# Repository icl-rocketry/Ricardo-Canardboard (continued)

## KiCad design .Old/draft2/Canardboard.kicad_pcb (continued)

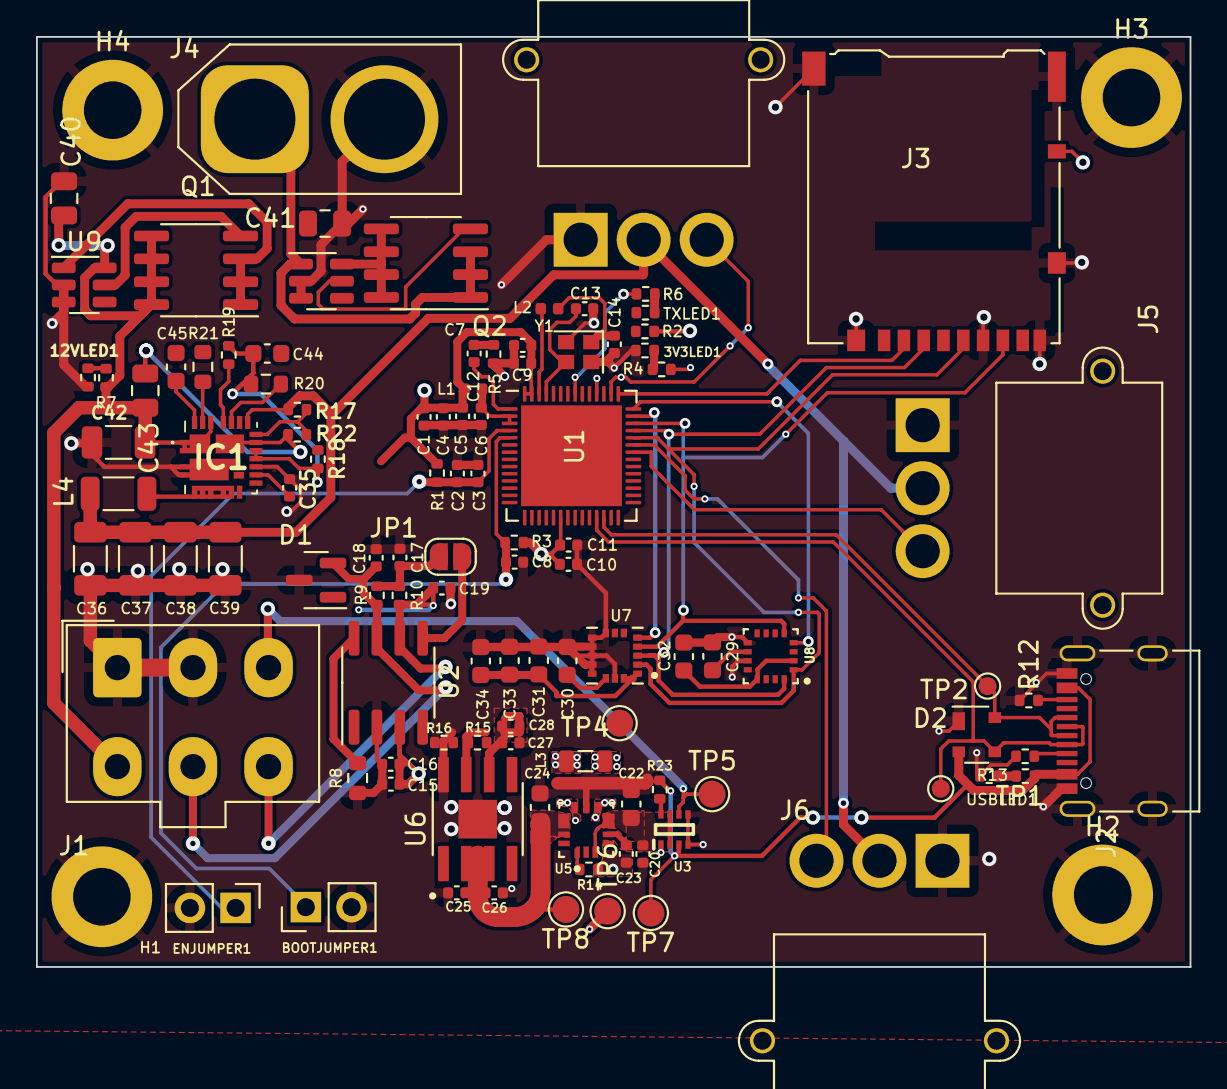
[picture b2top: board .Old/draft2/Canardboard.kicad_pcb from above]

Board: 4 copper layers, 64.1 x 51.7 mm, 111 parts (0 on the bottom side), 63 nets.

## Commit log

2022-11-08 initial commit
    started repo for canards
2022-11-11 tidied up
2022-11-22 used new esp32 board
2023-01-24 pcb roughly organized
    andrei updated his board agaain
2023-01-24 made everything smaller
    :)
2023-01-31 silk screen
2023-01-31 31/01/23
2023-02-02 02/02/23
2023-02-04 04/02/2023
2023-02-07 07/02/23
2023-02-10 changes
    ch
2023-02-11 11/02/23
2023-03-31 3rd iteration started
    - mosfet capacitor sized to be super big https://jlcpcb.com/partdetail/Lelon-VEJ222M1ETR1616/C249624
    - Inductor https://www.mouser.co.uk/ProductDetail/Walsin/WLPMA0A040M2R2LC?qs=sGAEpiMZZMv126LJFLh8y9BXdD8xymaqIlTb7%2F69fTY%3D
    - Buck input capacitors and output capacitors sized, 3x 47uF for both
    Buck:
    - R_FB_H 34kOhms
    - R_FB_L 3kOhms
2023-03-31 first draft of PCB layout
2023-04-01 error encountered - battery logic and inductor
    - use large capacitor?
    - use VBUS as a power source?
2023-04-03 power draft 2, power fixed I think
    10 mosfets now!
    2 each on:
    Servo power: 3s/4s LIPO, RBUS_DEPL
    3.3: VBUS, RBUS_3.3, 3s/4s LIPO
    fixed some capacitors
2023-04-04 PCB layout work
    pcb layout work
2023-05-20 schematic review updated
    fixed:
    -pin 1 on the bootjumper is missing a connection.
    - Move the SD card to a 2nd SPI bus (so a 2nd set of MISO, MOSI, SCLK) as the rest of the bus is blocked while data is written to it, which would interrupt sensor readings.
    - Add a pull-up resistor on the DET_A pin of the micro SD card, and also connect that pin to the esp32 (picture from pickle)
    - VDD on the IMU (U7) is not connected to any power, should be connected to 3.3V
    - Turns out CAN capacitors C18, C19 actually aren’t needed. It’s up to you if you want to keep them, but if you do keep them could you change their value to “DNP” (stands for Do not place)
2023-05-20 I don't want to lose all my changes so I will commit, commit.
2023-05-20 First PCB layout draft
    I need to learn how to properly do fills
2023-05-27 i dont know
2023-05-27 weird 3v3 and 3.3v bug
2023-05-28 almost all drc fixed (65 left)
    - J2 hole intersects with pads? USB
    - 3.3 regulator courtyard self intersecting?
    - courtyard overlaps (does this matter?)
    - padstack not valid? this is testpoints on the back with traces on the back, why is this bad?
    - expected SMD actual through hole?
    - front solder mask bridges items ?? testpoitns are on back layer
2023-06-01 everything should be fine
    fixed all mask stuff
2023-06-03 fixed all of andrei's comments v1
2023-06-16 roddy changes
2023-06-16 did some stuffus
    added a new power plane in servo power on the back side
    made SW larger
    and a lot more changes
2023-06-18 latest channges
    dont understand why making more copper is good for thermal
2023-06-20 all DRC fixed
    andrei hih ih ihi hi hi h
2023-06-20 final andrei changes
    lol
2023-07-01 silkscreen update
2023-07-01 i forgot to save the silkscreen update
2023-07-01 more vias
2023-07-01 funny wow
    funny wow
2023-07-07 new board just dropped
    i hate my life
2023-07-07 some sw stuff
    stuff
2023-07-07 lmao funny
    hi
2023-07-09 final fixes mybe
2023-07-10 fixed via bypass capacitors
2023-07-10 final final changes
2023-07-15 bending calcs
    bending calcs
2023-08-11 ordering changes
2023-09-24 hmmmm
    whoever's reading this, you love my commits don't you?
2023-09-25 pushing for some reason
    yea
2023-09-26 i hate you
    i hate you pc for deleting EVERY CHANGES I MADE
2023-09-27 yeaaaaaaa
2023-10-03 its been a while
    this is very late push
2023-10-03 Updated submodule Firmware/components/libriccore
2023-10-03 Updated submodule Firmware/components/librnp
2023-10-04 moving average starting
    a
2023-10-04 WIP moving average
2023-10-04 tried a bit
2023-10-04 I think this is the first committed working version
2023-10-05 geddan logger works!
2023-10-05 moving average seems to be working with rand
2023-10-06 final code - raft 1
    yes
2023-10-11 last commit before launch!
2024-09-12 Added 3d Models
2024-09-24 nrcgeddan updated for single servo, component updates
2024-09-24 changed logging behaviour
2024-10-10 oops
2024-10-10 buck behaviour update
2024-10-10 going to zero when disarm called
